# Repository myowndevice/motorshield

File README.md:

## Плата управления моторами постоянного тока

Любой робот содержит моторы, и ими надо управлять. Данная плата управления моторами может управлять 4-мя моторами постоянного тока напряжением от 7 до 12В и максимальным током до 1.5А каждый. Каждый мотор управляется полным H-мостом на основе полевых транзисторов MOSFET, что позволяет управлять скоростью и направлением вращения мотора с максимальным КПД.
Управление моторами осуществляет собственный микроконтроллер. Благодаря этому необходим всего один провод. Для управления достаточно передать сразу нужную скорость от -127 до +127. Команды передаются по протоколу UART и защищены от помех контрольной суммой. Кроме данного управляющего сигнала на основной разъем выведен полный UART, I2C, SWIM и питание 5В.
Прошивку в МК можно загрузить по протоколу UART, если у вас нет ST-Link. Выход 5В может выдать до 500ма тока, что позволяет питать «главный» процессор робота непосредственно с этой платы. Мощности выбранного МК хватит на решение всех задач связанных с регулированием скорости и направления вращения моторов. Возможно подключение до 4-х датчиков оборотов колеса.

Ключевые параметры платы управления моторами:
- Небольшой размер
- Управление 4-мя моторами постоянного тока одновременно
- Сопротивление одного H-моста составляет всего 80 мОм.
- Рабочий ток каждого мотора не более 1.5А, напряжение не более 12В. Небольшое собственное потребление тока, для меньшего расхода батареек или аккумуляторов
- Напряжение питания от 7 до 12В</p>
- Выход 5В для питания основного	модуля, до 500 мА
- Управление по одному проводу —	протокол UART, всего один вывод для управления всеми моторами
- Независимое управление скоростью и направлением вращения каждого мотора
- Управление по шине I2C, подключение 2-х датчиков оборотов колес для контроля скорости и пройденного расстояния, управление сервами, чтение сигнала PPM с радио пульта управления.

Данный репозитарий содержит все необходимые файлы для платы управления моторами.Если вы будете скачивать файлы через web не забудьте скачать общую папку Kicadlib.

Ознакомится со схемой и подробным описанием данного прибора, программы, и порядка сборки можно, [прочитав эту подробную статью](http://myowndevice.ru/index.php/pribory/item/44-plata-upravleniya-motorami-postoyannogo-toka)

Также [здесь](http://myowndevice.ru) вы найдете подробное описание как сделать другие приборы, много теории о том, как их делать, методику изготовления печатных плат и много другого.

Изучай микроконтроллеры, делай платы дома, разрабатывай электронику сам!

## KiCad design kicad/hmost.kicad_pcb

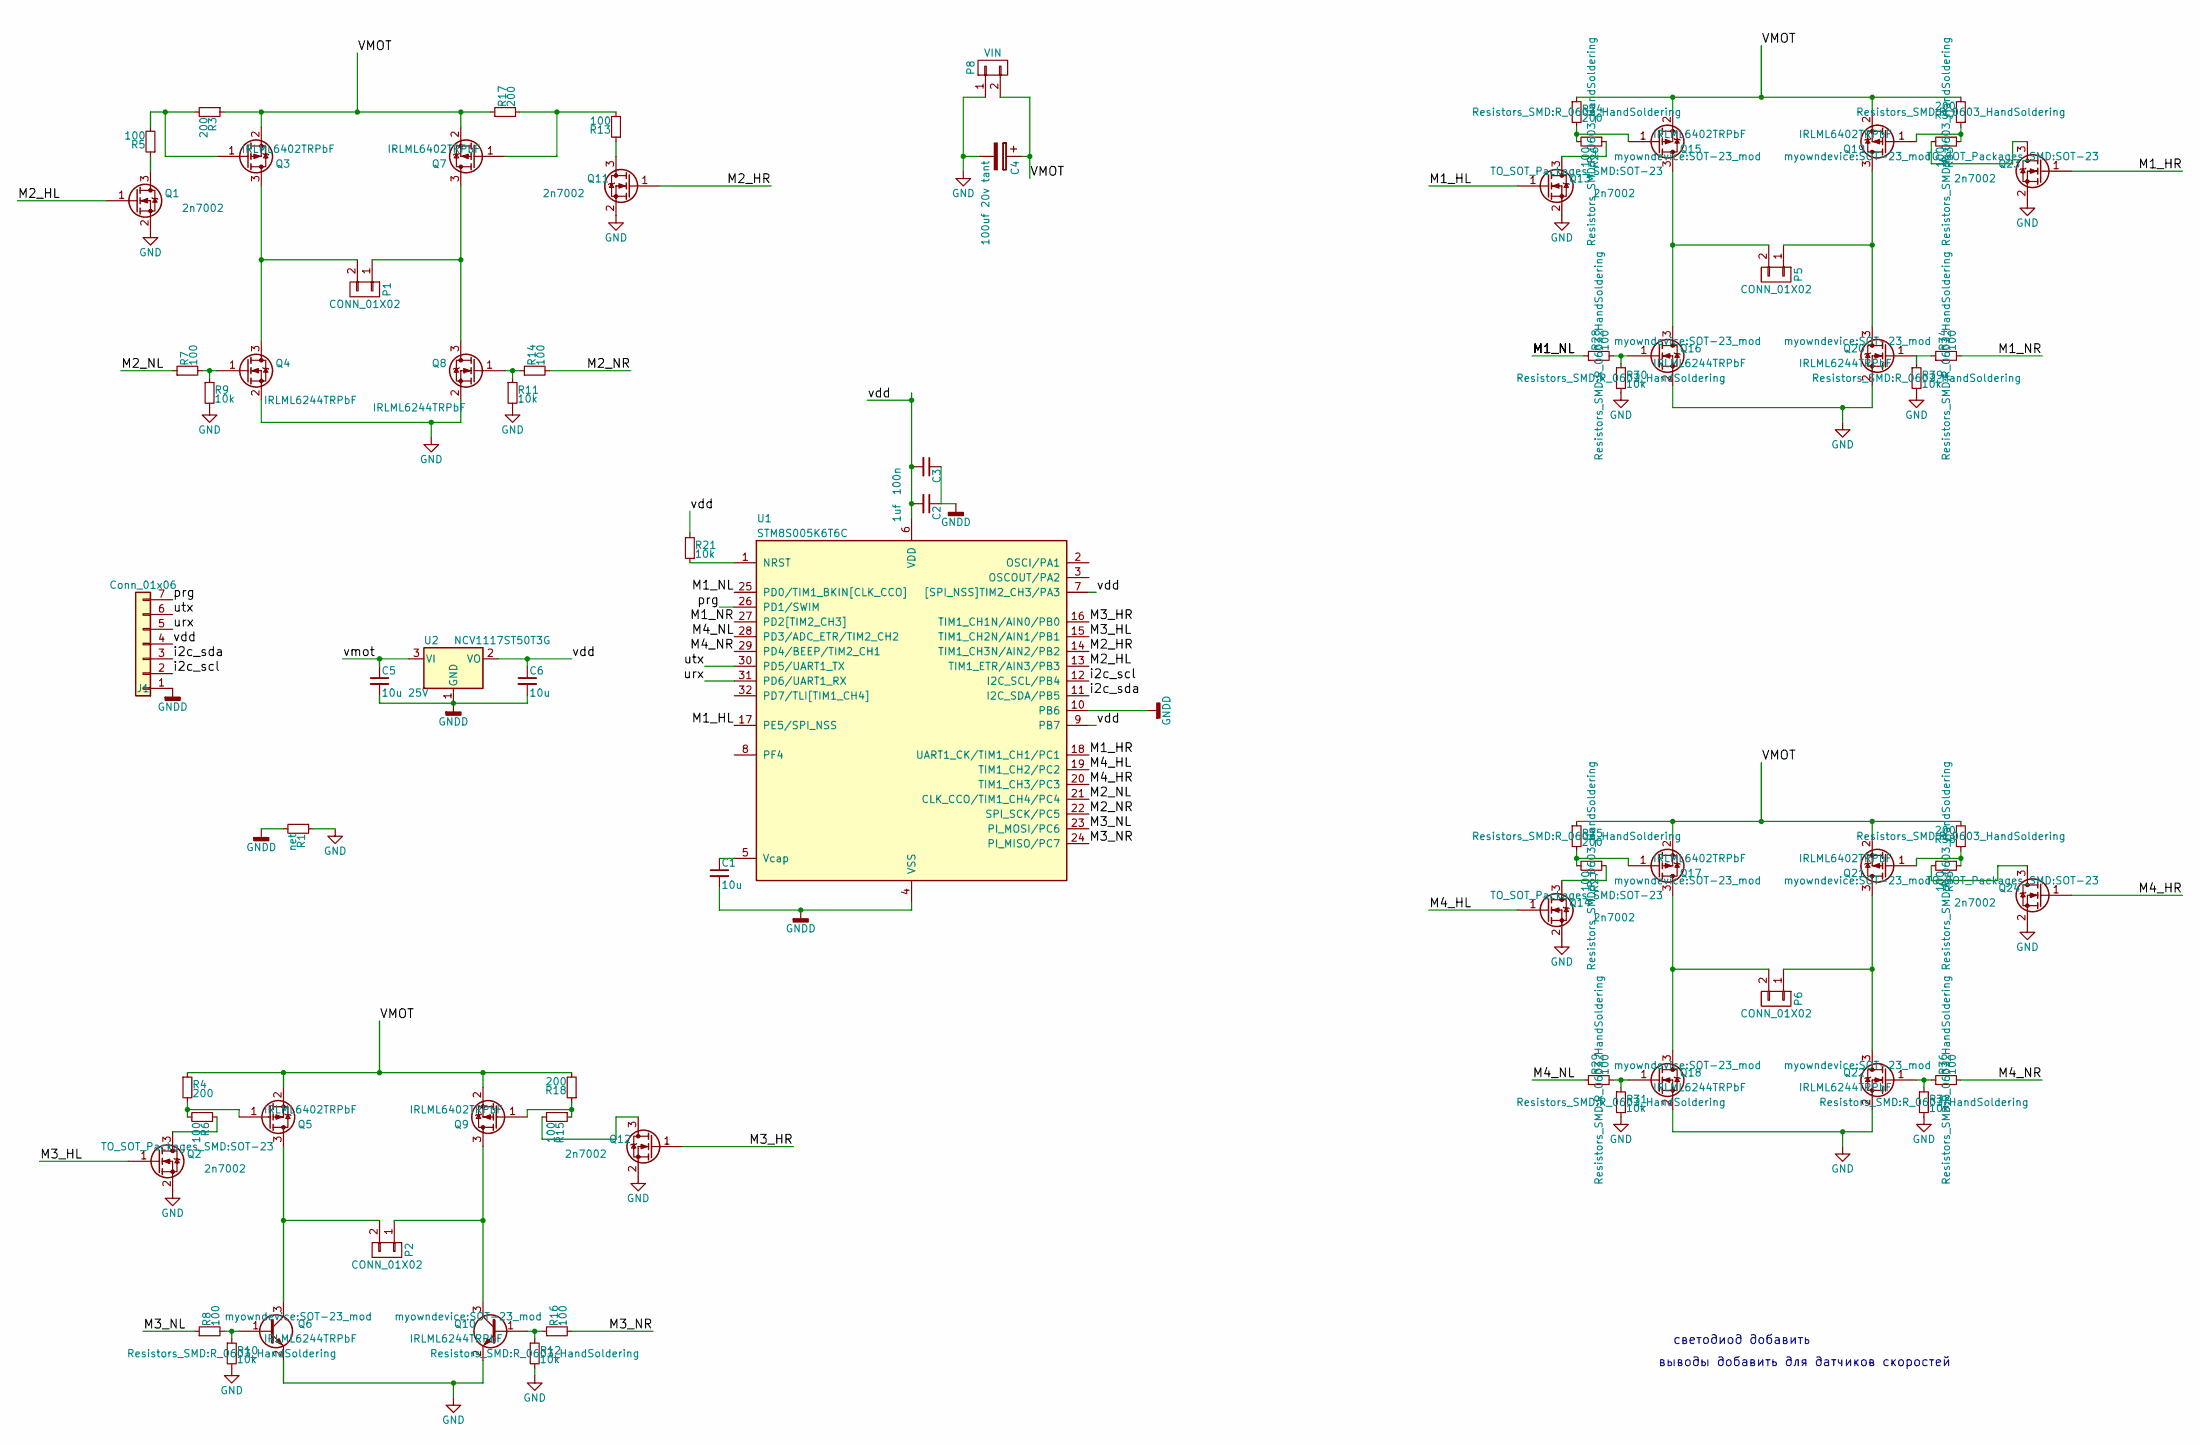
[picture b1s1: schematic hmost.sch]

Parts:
C1, C6: 10u; C_0805_HandSoldering
C2: 1uf; C_0805_HandSoldering
C3: 100n; C_0603_HandSoldering
C4: 100uf 20v tant; CP_Tantalum_Case-D_EIA-7343-31_Hand
C5: 10u 25V; C_0805_HandSoldering
J1: Conn_01x06; Pin_Header_Angled_1x07_Pitch2.54mm
P1, P2, P5, P6: CONN_01X02; TerminalBlock_bornier-2_P5.08mm
P8: VIN; TerminalBlock_bornier-2_P5.08mm
Q1, Q2, Q11, Q12, Q13, Q14, Q23, Q24: 2n7002; SOT-23
Q3, Q5, Q7, Q9, Q15, Q17, Q19, Q21: IRLML6402TRPbF; SOT-23_mod
Q4, Q6, Q8, Q10, Q16, Q18, Q20, Q22: IRLML6244TRPbF; SOT-23_mod
R1: net; smd_joint
R3, R4, R17, R18, R24, R25, R37, R38: 200; R_0603_HandSoldering
R5, R6, R7, R8, R13, R14, R15, R16, R26, R27, R28, R29, R33, R34, R35, R36: 100; R_0603_HandSoldering
R9, R10, R11, R12, R21, R30, R31, R32, R39: 10k; R_0603_HandSoldering
U1: STM8S005K6T6C; LQFP-32_05
U2: NCV1117ST50T3G; SOT-223

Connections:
/M1_HL: Q13.1 (G), U1.17 (PE5/SPI_NSS)
/M1_HR: Q23.1 (G), U1.18 (UART1_CK/TIM1_CH1/PC1)
/M1_NL: R28.1, U1.25 (PD0/TIM1_BKIN[CLK_CCO])
/M1_NR: R34.2, U1.27 (PD2[TIM2_CH3])
/M2_HL: Q1.1 (G), U1.13 (TIM1_ETR/AIN3/PB3)
/M2_HR: Q11.1 (G), U1.14 (TIM1_CH3N/AIN2/PB2)
/M2_NL: R7.1, U1.21 (CLK_CCO/TIM1_CH4/PC4)
/M2_NR: R14.2, U1.22 (SPI_SCK/PC5)
/M3_HL: Q2.1 (G), U1.15 (TIM1_CH2N/AIN1/PB1)
/M3_HR: Q12.1 (G), U1.16 (TIM1_CH1N/AIN0/PB0)
/M3_NL: R8.1, U1.23 (PI_MOSI/PC6)
/M3_NR: R16.2, U1.24 (PI_MISO/PC7)
/M4_HL: Q14.1 (G), U1.19 (TIM1_CH2/PC2)
/M4_HR: Q24.1 (G), U1.20 (TIM1_CH3/PC3)
/M4_NL: R29.1, U1.28 (PD3/ADC_ETR/TIM2_CH2)
/M4_NR: R36.2, U1.29 (PD4/BEEP/TIM2_CH1)
/VMOT: C4.1, C5.1, P8.2, Q3.2 (S), Q5.2 (S), Q7.2 (S), Q9.2 (S), Q15.2 (S), Q17.2 (S), Q19.2 (S), Q21.2 (S), R3.1, R4.1, R17.1, R18.2, R24.1, R25.1, R37.2, R38.2, U2.3 (VI)
/i2c_scl: J1.2, U1.12 (I2C_SCL/PB4)
/i2c_sda: J1.3, U1.11 (I2C_SDA/PB5)
/prg: J1.7, U1.26 (PD1/SWIM)
/urx: J1.5, U1.31 (PD6/UART1_RX)
/utx: J1.6, U1.30 (PD5/UART1_TX)
/vdd: C2.2, C3.2, C6.1, J1.4, R21.1, U1.6 (VDD), U1.7 ([SPI_NSS]TIM2_CH3/PA3), U1.9 (PB7), U2.2 (VO)
GND: C4.2, P8.1, Q1.2 (S), Q2.2 (S), Q4.2 (S), Q6.2 (E), Q8.2 (S), Q10.2 (E), Q11.2 (S), Q12.2 (S), Q13.2 (S), Q14.2 (S), Q16.2 (S), Q18.2 (S), Q20.2 (S), Q22.2 (S), Q23.2 (S), Q24.2 (S), R1.1, R9.2, R10.2, R11.2, R12.2, R30.2, R31.2, R32.2, R39.2
GNDD: C1.2, C2.1, C3.1, C5.2, C6.2, J1.1, R1.2, U1.4 (VSS), U1.10 (PB6), U2.1 (GND)
unnamed: C1.1, U1.5 (Vcap)
unnamed: P1.1, Q7.3 (D), Q8.3 (D)
unnamed: P1.2, Q3.3 (D), Q4.3 (D)
unnamed: P2.1, Q9.3 (D), Q10.3 (C)
unnamed: P2.2, Q5.3 (D), Q6.3 (C)
unnamed: P5.1, Q19.3 (D), Q20.3 (D)
unnamed: P5.2, Q15.3 (D), Q16.3 (D)
unnamed: P6.1, Q21.3 (D), Q22.3 (D)
unnamed: P6.2, Q17.3 (D), Q18.3 (D)
unnamed: Q1.3 (D), R5.1
unnamed: Q2.3 (D), R6.1
unnamed: Q3.1 (G), R3.2, R5.2
unnamed: Q4.1 (G), R7.2, R9.1
unnamed: Q5.1 (G), R4.2, R6.2
unnamed: Q6.1 (B), R8.2, R10.1
unnamed: Q7.1 (G), R13.2, R17.2
unnamed: Q8.1 (G), R11.1, R14.1
unnamed: Q9.1 (G), R15.1, R18.1
unnamed: Q10.1 (B), R12.1, R16.1
unnamed: Q11.3 (D), R13.1
unnamed: Q12.3 (D), R15.2
unnamed: Q13.3 (D), R26.1
unnamed: Q14.3 (D), R27.1
unnamed: Q15.1 (G), R24.2, R26.2
unnamed: Q16.1 (G), R28.2, R30.1
unnamed: Q17.1 (G), R25.2, R27.2
unnamed: Q18.1 (G), R29.2, R31.1
unnamed: Q19.1 (G), R33.1, R37.1
unnamed: Q20.1 (G), R34.1, R39.1
unnamed: Q21.1 (G), R35.1, R38.1
unnamed: Q22.1 (G), R32.1, R36.1
unnamed: Q23.3 (D), R33.2
unnamed: Q24.3 (D), R35.2
unnamed: R21.2, U1.1 (NRST)

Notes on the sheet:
светодиод добавить
выводы добавить для датчиков скоростей

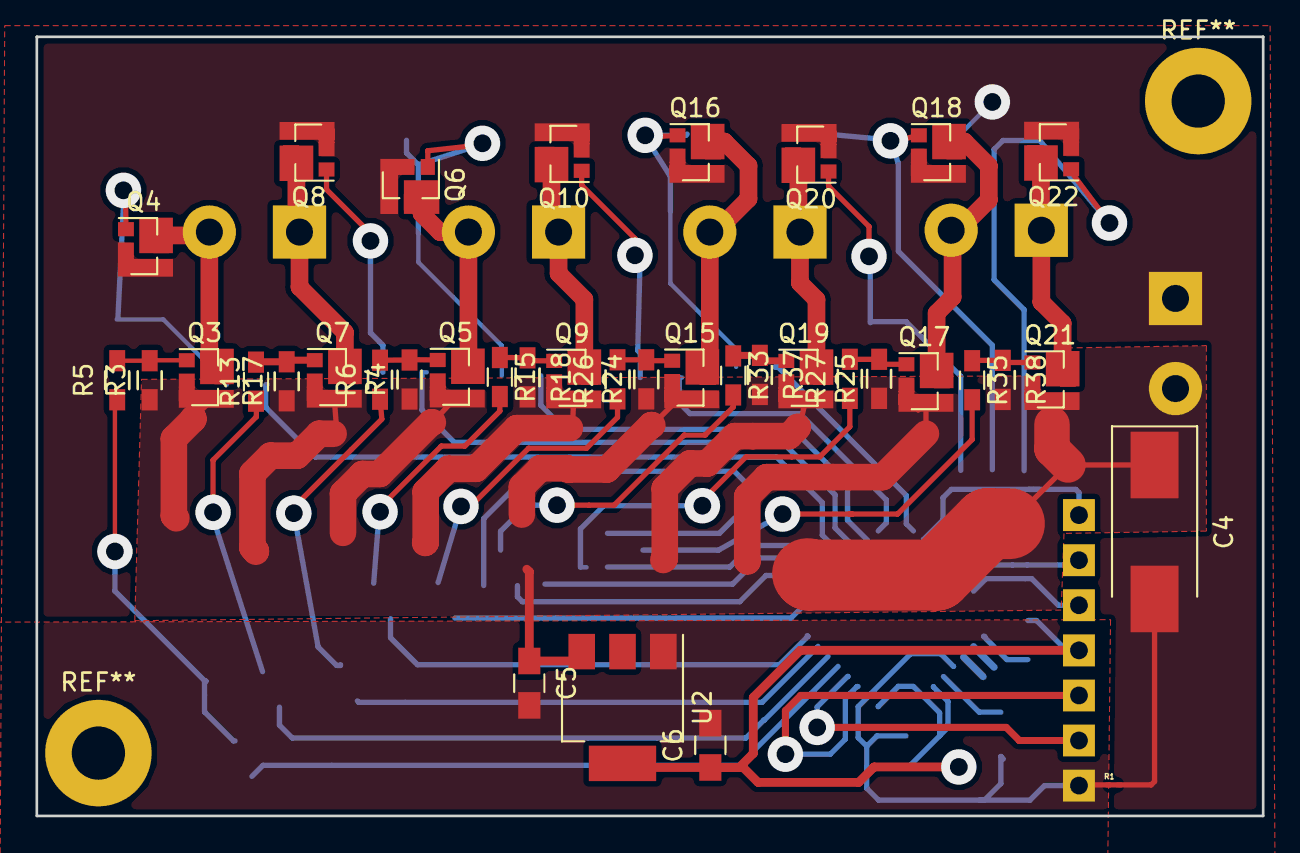
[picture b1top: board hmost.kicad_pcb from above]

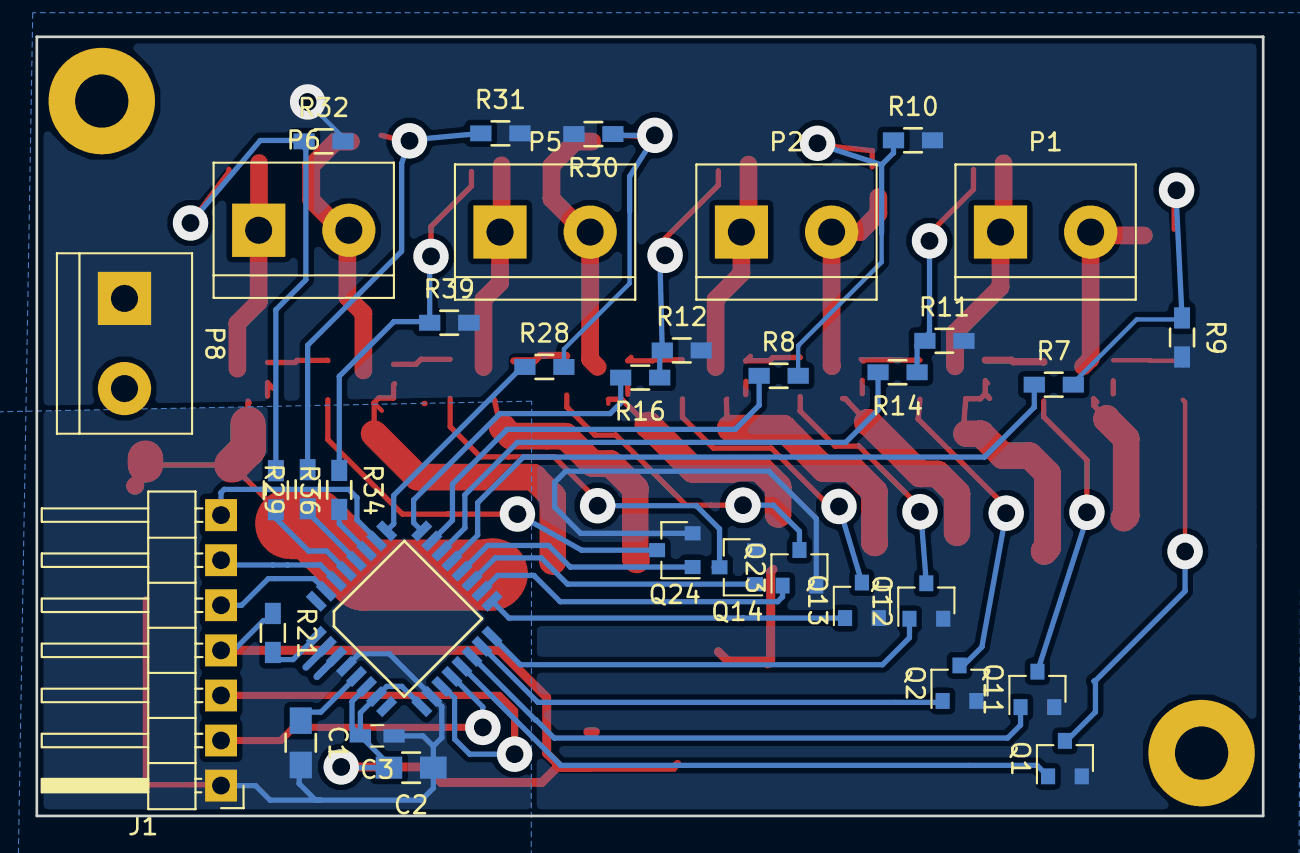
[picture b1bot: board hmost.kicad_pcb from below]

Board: 2 copper layers, 69.1 x 43.9 mm, 72 parts (35 on the bottom side), 59 nets.

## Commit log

2018-12-03 start
